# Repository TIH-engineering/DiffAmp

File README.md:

# DiffAmp

## 🔌 Leiterplattenbeschreibung

Die Leiterplatte **DiffAmp** dient zur praktischen Untersuchung von **Differenzverstärkern**. Sie ermöglicht den Vergleich einer diskret mit Transistoren aufgebauten Differenzverstärkerstufe mit einem Differenzverstärker auf Basis eines **Operationsverstärkers**.

Die Leiterplatte enthält zwei unterschiedliche Schaltungsvarianten:

- **Differenzverstärker mit zwei Bipolartransistoren**
- **Differenzverstärker mit Operationsverstärker (Subtrahierer)**

Der diskrete Differenzverstärker kann über Jumper in unterschiedlichen Betriebsarten betrieben werden. Die gemeinsame Emitterbeschaltung der beiden Transistoren kann wahlweise mit einem **Emitterwiderstand** oder mit einer **Stromquelle** realisiert werden. Dadurch lässt sich der Einfluss der Stromquellenschaltung auf das Verhalten des Differenzverstärkers praktisch untersuchen.

Zusätzliche Jumper ermöglichen unterschiedliche Messkonfigurationen zur Bestimmung der

- **Gegentaktverstärkung**
- **Gleichtaktverstärkung**

Damit können aus den Messwerten auch die Unterschiede zwischen Gegentakt- und Gleichtaktansteuerung sowie die **Gleichtaktunterdrückung** des Differenzverstärkers untersucht werden.

Als Vergleichsschaltung ist zusätzlich ein Differenzverstärker mit einem **LM358-Operationsverstärker** aufgebaut. Dieser arbeitet als Subtrahierer und bildet die Differenz der beiden Eingangssignale `In1` und `In2`.

Die verschiedenen Ausgangssignale der Schaltungen stehen an separaten Anschlüssen zur Verfügung und können beispielsweise mit einem **Oszilloskop** vermessen und miteinander verglichen werden.

> **Einsatzgebiet:** Laborübungen und Unterricht zu Differenzverstärkern, Operationsverstärkern, Gegentakt- und Gleichtaktverstärkung sowie Gleichtaktunterdrückung

---

## 📥 Downloads

| Datei | Beschreibung |
|---|---|
| 📄 [Schaltplan (PDF)](../../releases/latest/download/schematic.pdf) | Schaltplan der Leiterplatte |
| 🖨️ [Leiterplatte (PDF)](../../releases/latest/download/pcb.pdf) | Leiterplattenansicht als PDF |
| 🔩 [Bohrplan (PDF)](../../releases/latest/download/drill.pdf) | Bohrdaten / Bohrplan |
| 📋 [Stückliste (Excel)](../../releases/latest/download/bom.xlsx) | Bill of Materials |
| 🌐 [Interactive BOM](../../releases/latest/download/ibom.html) | Interaktive Bestückungsansicht |
| 📦 [Fertigungsdaten](../../releases/latest/download/kicad.zip) | Gerber- und Bohrdaten |
| 🧊 [STEP-Modell](../../releases/latest/download/pcb.step) | 3D-Modell der Leiterplatte |

Die Dateien werden automatisch durch den Release-Workflow erzeugt.

---

## 🖥️ Leiterplatte

### Vorschau

| Oberseite | Unterseite |
|:---:|:---:|
|  |  |

### Oberseite

### Unterseite

---

## ℹ️ Projektinformationen

| Eigenschaft | Wert |
|---|---|
| **Projekt** | DiffAmp |
| **Software** | KiCad 10 |
| **Repository** | github.com/TIH-engineering/DiffAmp |
| **Autor** | TIH |
| **Lizenz** | CC BY-NC-SA 4.0 |

---

## 🗂️ Repository-Struktur

```text
.
├── .github/
│   └── workflows/       # GitHub Actions
├── .kibot/              # KiBot-Konfiguration
├── pcb/
│   ├── lib/             # Projektspezifische Bibliotheken
│   └── ...              # KiCad-Projektdateien
├── .gitignore
├── LICENSE
└── README.md

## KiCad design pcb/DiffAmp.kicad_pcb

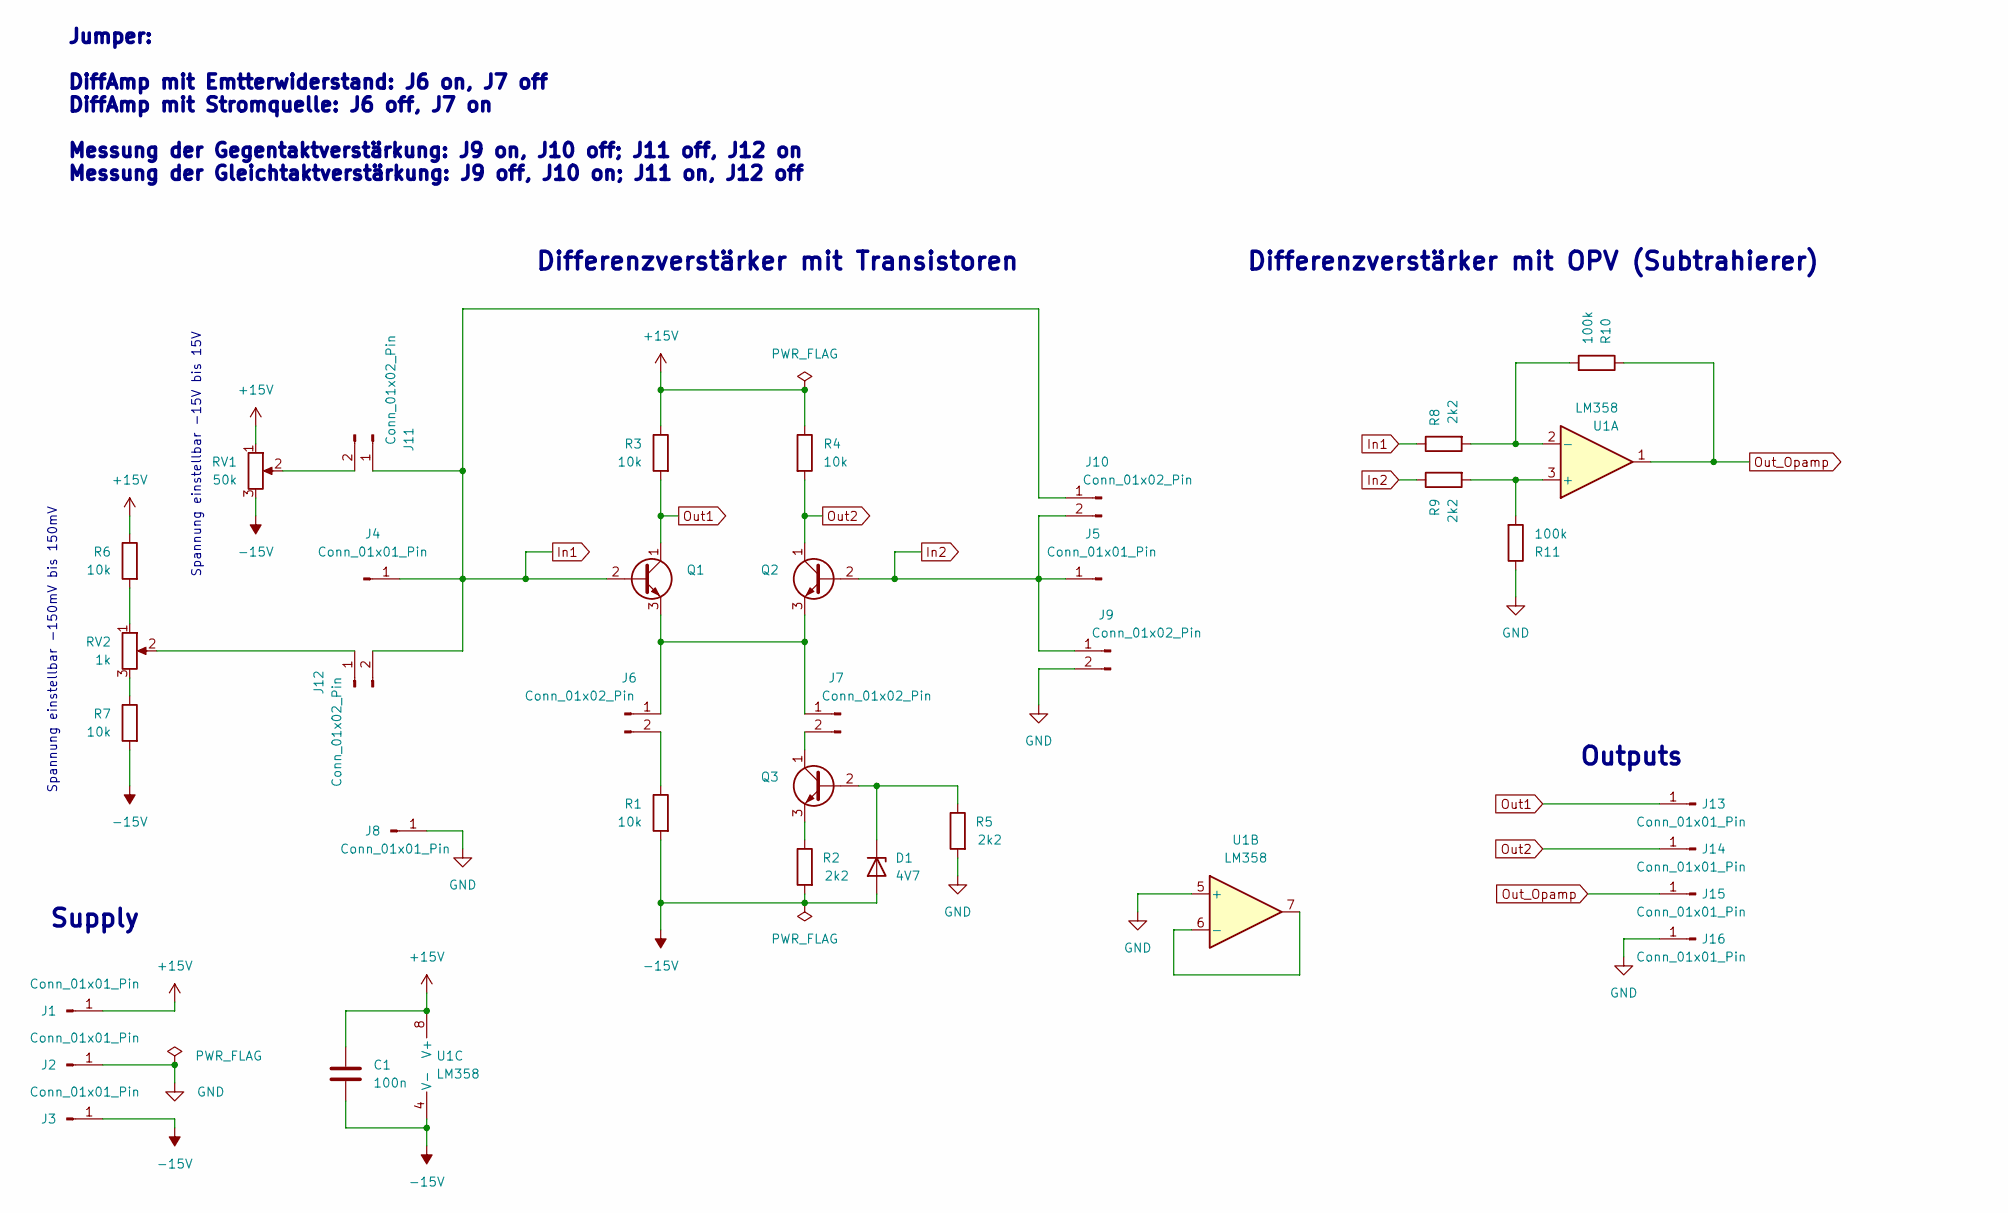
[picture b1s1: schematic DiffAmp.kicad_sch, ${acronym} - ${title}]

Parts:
C1: 100n; C_Disc_D3.8mm_W2.6mm_P2.50mm
D1: 4V7; D_A-405_P10.16mm_Horizontal
J1, J2, J3, J4, J5, J8, J13, J14, J15, J16: Conn_01x01_Pin; PinHeader_1x01_P2.54mm_Vertical
J6, J7, J9, J10, J11, J12: Conn_01x02_Pin; PinHeader_1x02_P2.54mm_Vertical
Q1, Q2, Q3: BC547; TO-92_Inline_Wide
R1, R3, R4, R6, R7: 10k; R_Axial_DIN0207_L6.3mm_D2.5mm_P10.16mm_Horizontal
R2, R5, R8, R9: 2k2; R_Axial_DIN0207_L6.3mm_D2.5mm_P10.16mm_Horizontal
R10, R11: 100k; R_Axial_DIN0207_L6.3mm_D2.5mm_P10.16mm_Horizontal
RV1: 50k; Potentiometer_Bourns_3005_Horizontal
RV2: 1k; Potentiometer_Bourns_3005_Horizontal
U1: LM358; DIP-8_W7.62mm

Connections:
+15V: C1.1, J1.1 (Pin_1_1), R3.1, R4.1, R6.1, RV1.1, U1.8 (V+)
-15V: C1.2, D1.2 (A), J3.1 (Pin_1_1), R1.2, R2.2, R7.2, RV1.3, U1.4 (V-)
GND: J2.1 (Pin_1_1), J8.1 (Pin_1_1), J9.2, J16.1 (Pin_1_1), R5.2, R11.1, U1.5 (+)
In1: J4.1 (Pin_1_1), J10.1, J11.1, J12.2, Q1.2 (B), R8.1
In2: J5.1 (Pin_1_1), J9.1, J10.2, Q2.2 (B), R9.1
unnamed: D1.1 (K), Q3.2 (B), R5.1
unnamed: J6.1, J7.1, Q1.3 (E), Q2.3 (E)
unnamed: J6.2, R1.1
unnamed: J7.2, Q3.1 (C)
unnamed: J11.2, RV1.2
unnamed: J12.1, RV2.2
unnamed: Q3.3 (E), R2.1
unnamed: R6.2, RV2.1
unnamed: R7.1, RV2.3
unnamed: R9.2, R11.2, U1.3 (+)
unnamed: R8.2, R10.2, U1.2 (-)
unnamed: U1.6 (-), U1.7
Out1: J13.1 (Pin_1_1), Q1.1 (C), R3.2
Out2: J14.1 (Pin_1_1), Q2.1 (C), R4.2
Out_Opamp: J15.1 (Pin_1_1), R10.1, U1.1

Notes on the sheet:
Spannung einstellbar -15V bis 15V
Supply
Outputs
Spannung einstellbar -150mV bis 150mV
Jumper: DiffAmp mit Emtterwiderstand: J6 on, J7 off DiffAmp mit Stromquelle: J6 off, J7 on Messung der Gegentaktverstärkung: J9 on, J10 off; J11 off, J12 on Messung der Gleichtaktverstärkung: J9 off, J10 on; J11 on, J12 off
Differenzverstärker mit Transistoren
Differenzverstärker mit OPV (Subtrahierer)

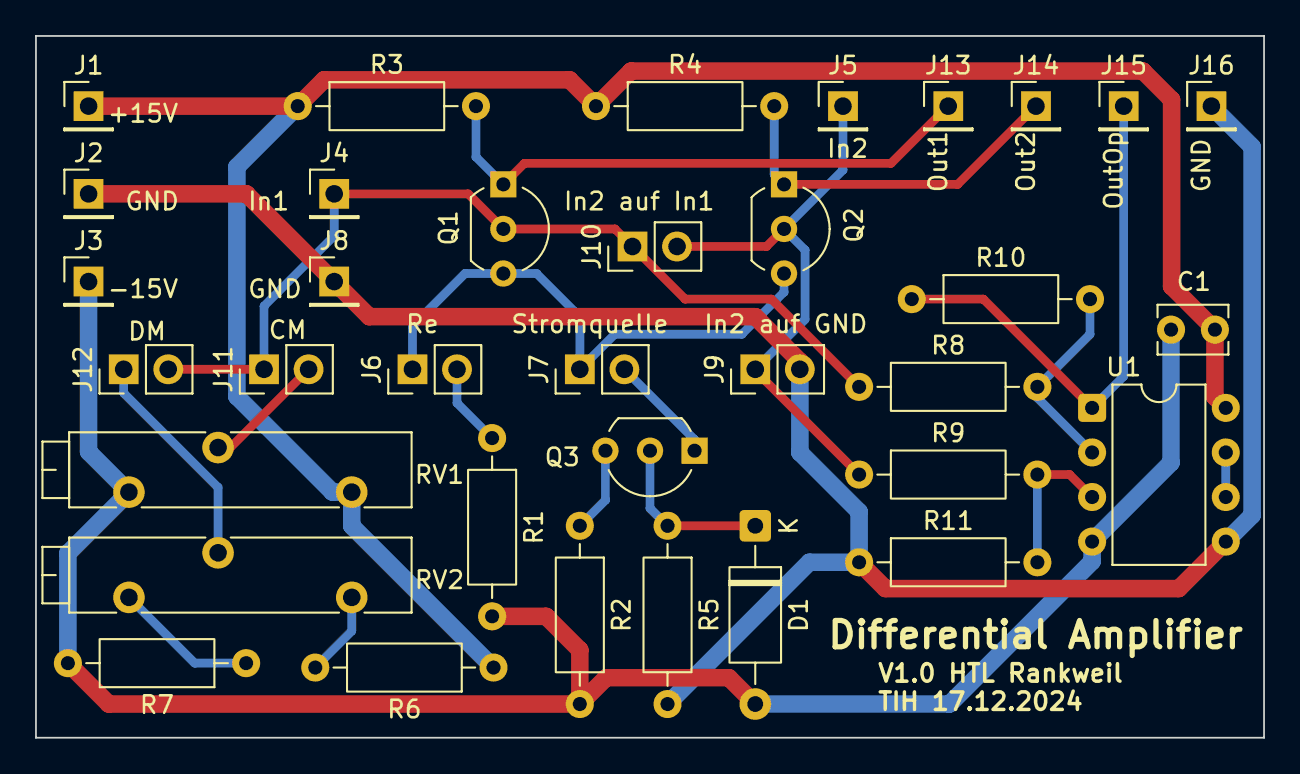
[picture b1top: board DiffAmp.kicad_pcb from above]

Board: 2 copper layers, 70.0 x 40.0 mm, 35 parts (0 on the bottom side), 20 nets.

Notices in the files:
README.md:
License: CC-BY-NC-SA-4.0
